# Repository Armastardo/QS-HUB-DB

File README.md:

# QS-HUB-DB
DB with a hub

Heavily based of 4pplet's SHKB Lite: https://github.com/4pplet/SHKB

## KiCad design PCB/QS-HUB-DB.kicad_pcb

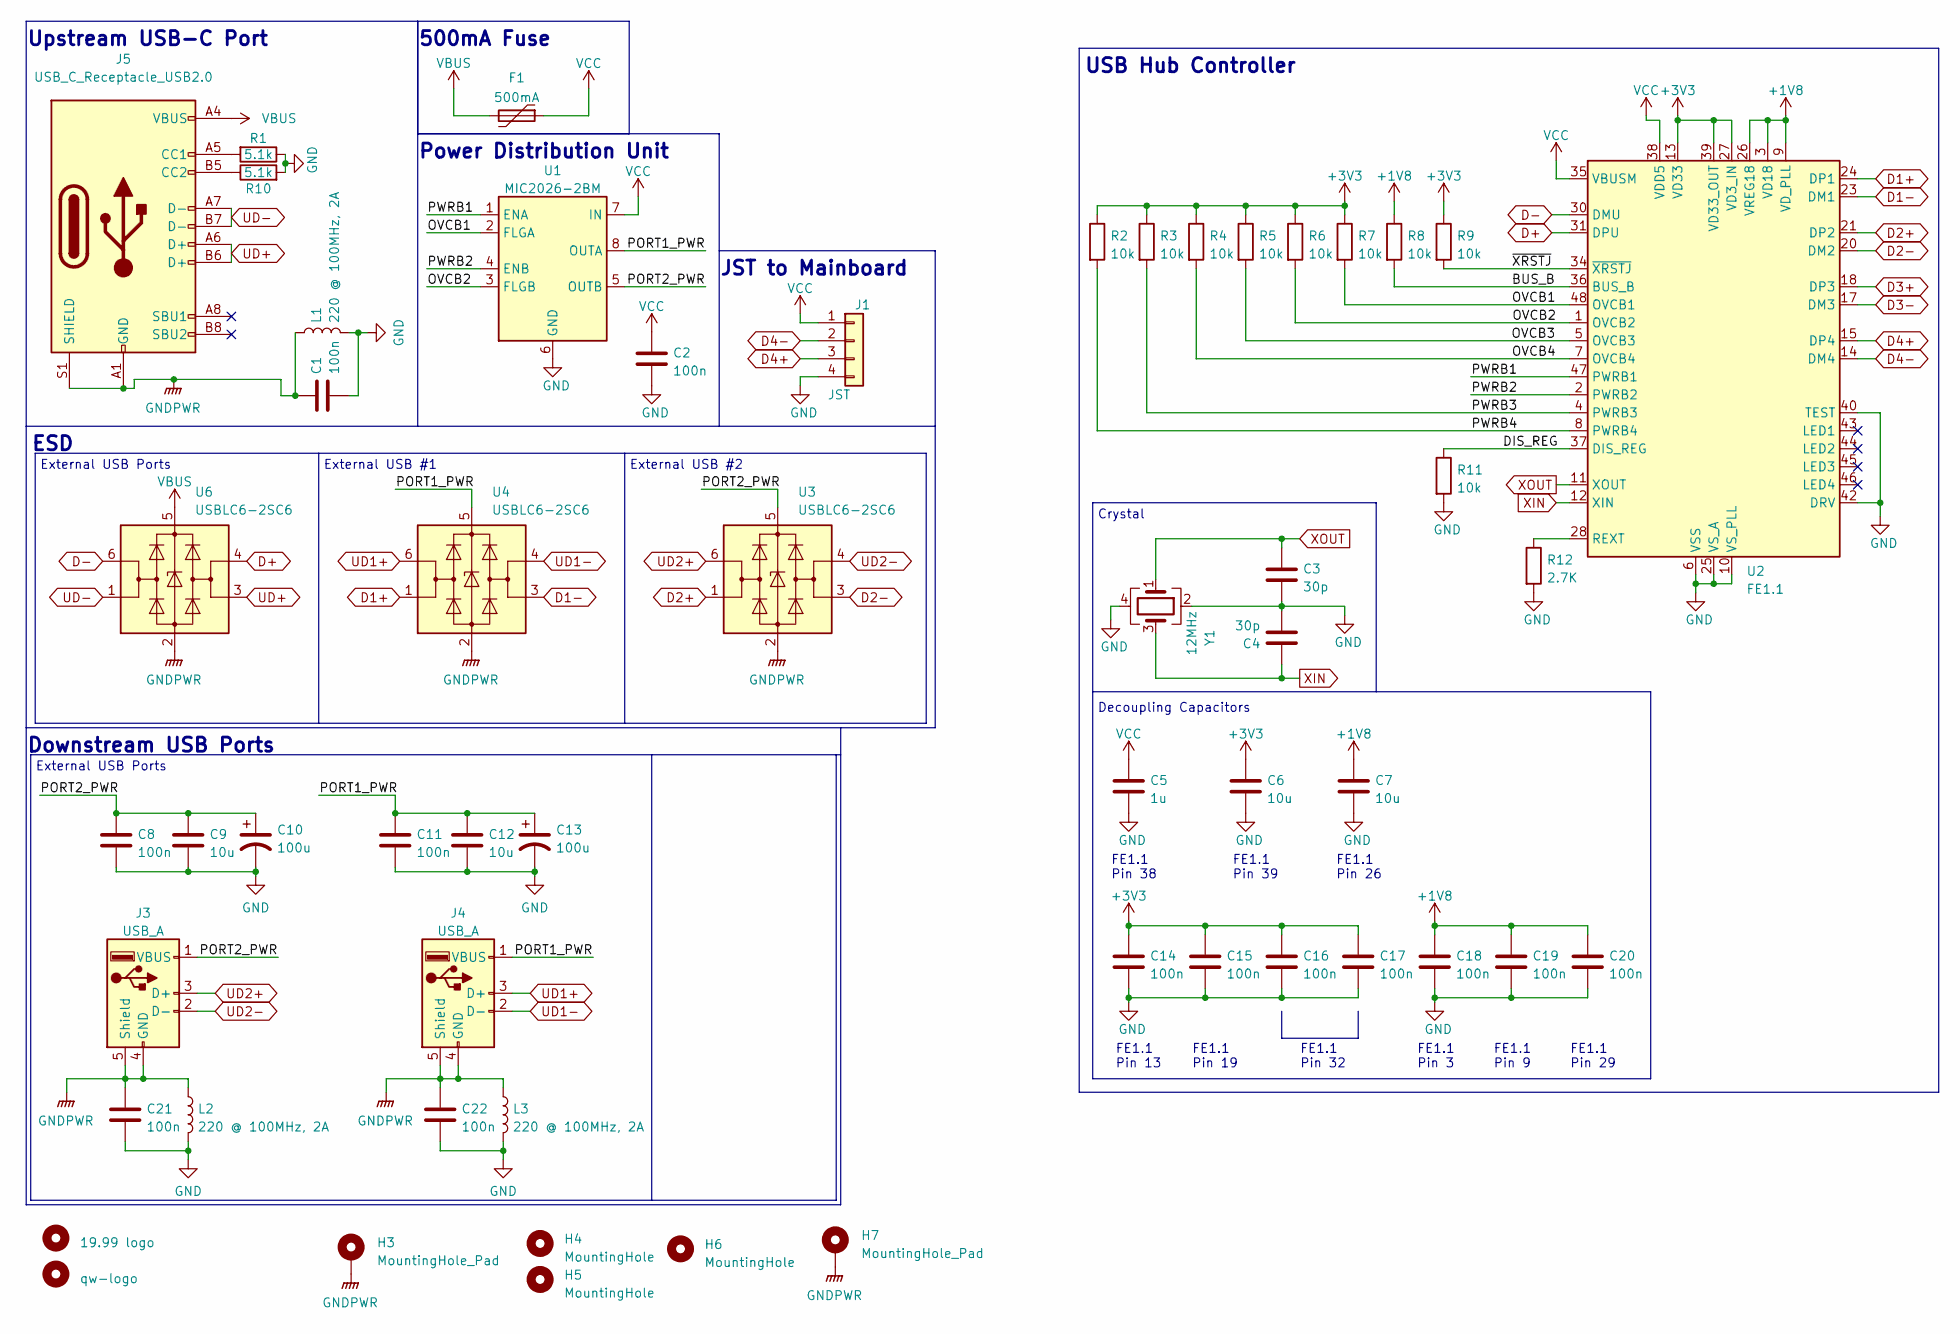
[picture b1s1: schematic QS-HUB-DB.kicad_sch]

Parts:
C1, C2, C8, C11, C14, C15, C16, C17, C18, C19, C20, C21, C22: 100n; C_0603_1608Metric; LCSC C14663
C3, C4: 30p; C_0603_1608Metric; LCSC C1658
C5: 1u; C_0603_1608Metric; LCSC C15849
C6, C7, C9, C12: 10u; C_0603_1608Metric; LCSC C19702
C10, C13: 100u; CP_Elec_6.3x5.9; LCSC C134878
F1: 500mA; Fuse_1206_3216Metric; LCSC C70076
H1: 19.99 logo; 1999 logo md
H2: qw-logo; qw new logo silk + copper sm
H3, H7: MountingHole_Pad; MountingHole_2.2mm_M2_DIN965_Pad
H4, H5, H6: MountingHole; MountingHole_2.2mm_M2_DIN965
J1: JST; JST_SH_SM04B-SRSS-TB_1x04-1MP_P1.00mm_Horizontal; LCSC C145956
J3, J4: USB_A; USB_A_Molex_67643_Horizontal; LCSC C718022
J5: USB_C_Receptacle_USB2.0; USB_C_Receptacle_HRO_TYPE-C-31-M-12
L1, L2, L3: 220 @ 100MHz, 2A; L_0603_1608Metric; LCSC C85832
R1, R10: 5.1k; R_0402_1005Metric; LCSC C25905
R2, R3, R4, R5, R6, R7, R8, R9, R11: 10k; R_0603_1608Metric; LCSC C25804
R12: 2.7K; R_0603_1608Metric; LCSC C13167
U1: MIC2026-2BM; SOIC-8_3.9x4.9mm_P1.27mm; LCSC C148072
U2: FE1.1; LQFP-48_7x7mm_P0.5mm; LCSC C28958
U3, U4, U6: USBLC6-2SC6; SOT-23-6
Y1: 12MHz; Crystal_SMD_3225-4Pin_3.2x2.5mm; LCSC C9002

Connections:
+1V8: C7.1, C18.1, C19.1, C20.1, R8.1, U2.3 (VD18), U2.9 (VD_PLL), U2.26 (VREG18), U2.29 (VD18)
+3V3: C6.1, C14.1, C15.1, C16.1, C17.1, R2.1, R3.1, R4.1, R5.1, R6.1, R7.1, R9.1, U2.13 (VD33), U2.19 (VD33), U2.27 (VD3_IN), U2.32 (VD33), U2.39 (VD33_OUT), U2.41 (VD33)
/BUS_B: R8.2, U2.36 (BUS_B)
/DIS_REG: R11.1, U2.37 (DIS_REG)
/OVCB1: R7.2, U1.2 (FLGA), U2.48 (OVCB1)
/OVCB2: R6.2, U1.3 (FLGB), U2.1 (OVCB2)
/OVCB3: R5.2, U2.5 (OVCB3)
/OVCB4: R4.2, U2.7 (OVCB4)
/PORT1_PWR: C11.1, C12.1, C13.1, J4.1 (VBUS), U1.8 (OUTA), U4.5 (VBUS)
/PORT2_PWR: C8.1, C9.1, C10.1, J3.1 (VBUS), U1.5 (OUTB), U3.5 (VBUS)
/PWRB1: U1.1 (ENA), U2.47 (PWRB1)
/PWRB2: U1.4 (ENB), U2.2 (PWRB2)
/PWRB3: R3.2, U2.4 (PWRB3)
/PWRB4: R2.2, U2.8 (PWRB4)
/~XRSTJ: R9.2, U2.34 (~XRSTJ)
D1+: U2.24 (DP1), U4.1 (I/O1)
D1-: U2.23 (DM1), U4.3 (I/O2)
D2+: U2.21 (DP2), U3.1 (I/O1)
D2-: U2.20 (DM2), U3.3 (I/O2)
D3+: U2.18 (DP3)
D3-: U2.17 (DM3)
D4+: J1.3, U2.15 (DP4)
D4-: J1.2, U2.14 (DM4)
D+: U2.31 (DPU), U6.4 (I/O2)
D-: U2.30 (DMU), U6.6 (I/O1)
GND: C1.2, C2.2, C3.2, C4.2, C5.2, C6.2, C7.2, C8.2, C9.2, C10.2, C11.2, C12.2, C13.2, C14.2, C15.2, C16.2, C17.2, C18.2, C19.2, C20.2, C21.2, C22.2, J1.4, L1.2, L2.2, L3.2, R1.1, R10.2, R11.2, R12.2, U1.6 (GND), U2.6 (VSS), U2.10 (VS_PLL), U2.16 (VSS), U2.22 (VSS), U2.25 (VS_A), U2.33 (VSS), U2.40 (TEST), U2.42 (DRV), Y1.2, Y1.4
GNDPWR: C1.1, C21.1, C22.1, H3.1, H7.1, J3.4 (GND), J3.5 (Shield), J4.4 (GND), J4.5 (Shield), J5.A1 (GND), J5.A12 (GND), J5.B1 (GND), J5.B12 (GND), J5.S1 (SHIELD), L1.1, L2.1, L3.1, U3.2 (GND), U4.2 (GND), U6.2 (GND)
unnamed: J5.A5 (CC1), R1.2
unnamed: J5.B5 (CC2), R10.1
unnamed: R12.1, U2.28 (REXT)
UD1+: J4.3 (D+), U4.6 (I/O1)
UD1-: J4.2 (D-), U4.4 (I/O2)
UD2+: J3.3 (D+), U3.6 (I/O1)
UD2-: J3.2 (D-), U3.4 (I/O2)
UD+: J5.A6 (D+), J5.B6 (D+), U6.3 (I/O2)
UD-: J5.A7 (D-), J5.B7 (D-), U6.1 (I/O1)
VBUS: F1.2, J5.A4 (VBUS), J5.A9 (VBUS), J5.B4 (VBUS), J5.B9 (VBUS), U6.5 (VBUS)
VCC: C2.1, C5.1, F1.1, J1.1, U1.7 (IN), U2.35 (VBUSM), U2.38 (VDD5)
XIN: C4.1, U2.12 (XIN), Y1.3
XOUT: C3.1, U2.11 (XOUT), Y1.1

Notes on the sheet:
Power Distribution Unit
External USB Ports
FE1.1 Pin 3
FE1.1 Pin 19
FE1.1 Pin 39
External USB #2
FE1.1 Pin 26
FE1.1 Pin 13
External USB #1
Crystal
ESD
FE1.1 Pin 9
Upstream USB-C Port
Downstream USB Ports
JST to Mainboard
Decoupling Capacitors
FE1.1 Pin 32
500mA Fuse
FE1.1 Pin 38
FE1.1 Pin 29
USB Hub Controller

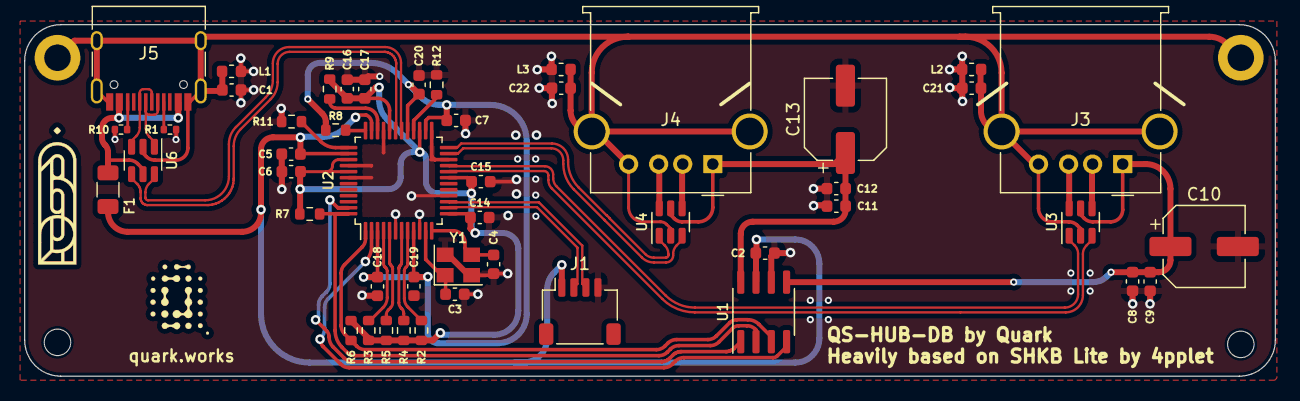
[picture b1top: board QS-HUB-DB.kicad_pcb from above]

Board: 2 copper layers, 104.0 x 29.2 mm, 54 parts (0 on the bottom side), 38 nets.

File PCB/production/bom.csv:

Designator,Footprint,Quantity,Value,LCSC Part #
"C1, C11, C14, C15, C16, C17, C18, C19, C2, C20, C21, C22, C8",0603,13,100n,C14663
"C10, C13",CP_Elec_6.3x5.9,2,100u,C134878
"C12, C6, C7, C9",0603,4,10u,C19702
"C3, C4",0603,2,30p,C1658
C5,0603,1,1u,C15849
F1,1206,1,500mA,C70076
H1,1999 logo md,1,19.99 logo,
H2,qw new logo silk + copper sm,1,qw-logo,
"H3, H7",MountingHole_2.2mm_M2_DIN965_Pad,2,MountingHole_Pad,
"H4, H5",MountingHole_2.2mm_M2_DIN965,2,MountingHole,
J1,JST_SH_SM04B-SRSS-TB_1x04-1MP_P1.00mm_Horizontal,1,JST,C145956
"J3, J4",USB_A_Molex_67643_Horizontal,2,USB_A,C718022
J5,USB_C_Receptacle_HRO_TYPE-C-31-M-12,1,USB_C_Receptacle_USB2.0,
"L1, L2, L3",0603,3,"220 @ 100MHz, 2A",C85832
"R1, R10",0402,2,5.1k,C25905
"R11, R2, R3, R4, R5, R6, R7, R8, R9",0603,9,10k,C25804
R12,0603,1,2.7K,C13167
U1,SOIC-8_3.9x4.9mm_P1.27mm,1,MIC2026-2BM,C148072
U2,LQFP-48_7x7mm_P0.5mm,1,FE1.1,C28958
"U3, U4, U6",SOT-23-6,3,USBLC6-2SC6,
Y1,Crystal_SMD_3225-4Pin_3.2x2.5mm,1,12MHz,C9002

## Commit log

2023-05-28 Added first revision
2023-06-17 Added 3D model and updated silk
